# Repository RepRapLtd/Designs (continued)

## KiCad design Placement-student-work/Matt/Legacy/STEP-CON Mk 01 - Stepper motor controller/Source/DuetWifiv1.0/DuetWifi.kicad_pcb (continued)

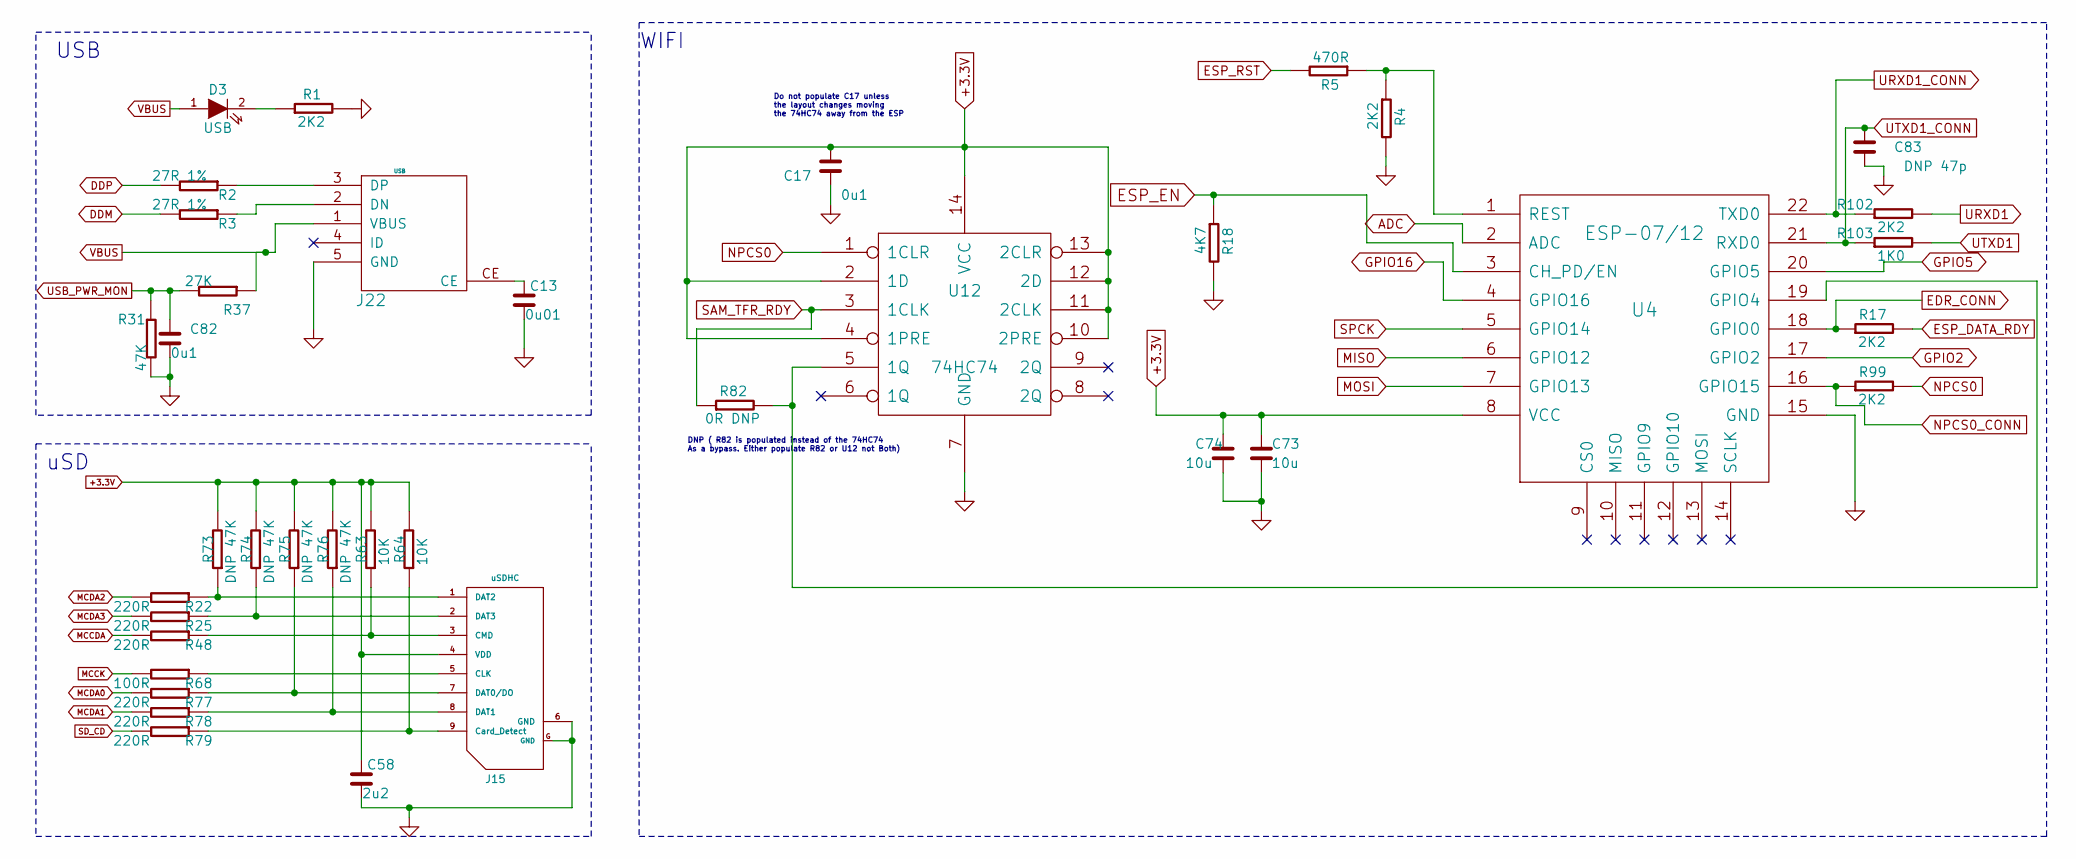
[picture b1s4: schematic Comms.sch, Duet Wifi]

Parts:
C13: 0u01; C_0603
C17, C82: 0u1; C_0603
C58: 2u2; C_0603
C73, C74: 10u; C_0805
C83: DNP 47p; C_0603
D3: USB; D_0603
J15: uSDHC; uSD_SKT
J22: USB; uUSB_new
R1, R4, R17, R99, R102: 2K2; R_0603
R2, R3: 27R 1%; R_0603
R5: 470R; R_0603
R18: 4K7; R_0603
R22, R25, R48, R77, R78, R79: 220R; R_0603
R31: 47K; R_0603
R37: 27K; R_0603
R63, R64: 10K; R_0603
R68: 100R; R_0603
R73, R74, R75, R76: DNP 47K; R_0603
R82: 0R DNP; R_0603
R103: 1K0; R_0603
U4: ESP-07/12; ESP-12E
U12: 74HC74; TSSOP-14

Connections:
+3.3V: C17.1, C58.1, C73.1, C74.1, J15.4 (VDD), R63.2, R64.2, R73.2, R74.2, R75.2, R76.2, U4.8 (VCC), U12.2 (1D), U12.4 (1PRE), U12.10 (2PRE), U12.11 (2CLK), U12.12 (2D), U12.13 (2CLR), U12.14 (VCC); also elsewhere on the board
ADC: U4.2 (ADC); also elsewhere on the board
DDM: R3.2; also elsewhere on the board
DDP: R2.2; also elsewhere on the board
EDR_CONN: R17.1, U4.18 (GPIO0); also elsewhere on the board
ESP_DATA_RDY: R17.2; also elsewhere on the board
ESP_EN: R18.1, U4.3 (CH_PD/EN); also elsewhere on the board
ESP_RST: R5.2; also elsewhere on the board
GND: C13.2, C17.2, C58.2, C73.2, C74.2, C82.2, C83.2, J15.6 (GND), J15.G (GND), J22.5 (GND), R1.2, R4.2, R18.2, R31.2, U4.15 (GND), U12.7 (GND); also elsewhere on the board
GPIO2: U4.17 (GPIO2); also elsewhere on the board
GPIO5: U4.20 (GPIO5); also elsewhere on the board
GPIO16: U4.4 (GPIO16); also elsewhere on the board
MCCDA: R48.2; also elsewhere on the board
MCCK: R68.2; also elsewhere on the board
MCDA0: R77.2; also elsewhere on the board
MCDA1: R78.2; also elsewhere on the board
MCDA2: R22.2; also elsewhere on the board
MCDA3: R25.2; also elsewhere on the board
MISO: U4.6 (GPIO12); also elsewhere on the board
MOSI: U4.7 (GPIO13); also elsewhere on the board
NPCS0: R99.2, U12.1 (1CLR); also elsewhere on the board
NPCS0_CONN: R99.1, U4.16 (GPIO15); also elsewhere on the board
unnamed: C13.1, J22.CE
unnamed: D3.2 (K), R1.1
unnamed: J15.1 (DAT2), R22.1, R73.1
unnamed: J15.2 (DAT3), R25.1, R74.1
unnamed: J15.3 (CMD), R48.1, R63.1
unnamed: J15.5 (CLK), R68.1
unnamed: J15.7 (DAT0/DO), R75.1, R77.1
unnamed: J15.8 (DAT1), R76.1, R78.1
unnamed: J15.9 (Card_Detect), R64.1, R79.1
unnamed: J22.2 (DN), R3.1
unnamed: J22.3 (DP), R2.1
unnamed: R4.1, R5.1, U4.1 (REST)
unnamed: R82.2, U4.19 (GPIO4), U12.5 (1Q)
SAM_TFR_RDY: R82.1, U12.3 (1CLK); also elsewhere on the board
SD_CD: R79.2; also elsewhere on the board
SPCK: U4.5 (GPIO14); also elsewhere on the board
URXD1: R102.2; also elsewhere on the board
URXD1_CONN: R102.1, U4.22 (TXD0); also elsewhere on the board
USB_PWR_MON: C82.1, R31.1, R37.2; also elsewhere on the board
UTXD1: R103.2; also elsewhere on the board
UTXD1_CONN: C83.1, R103.1, U4.21 (RXD0); also elsewhere on the board
VBUS: D3.1 (A), J22.1 (VBUS), R37.1; also elsewhere on the board

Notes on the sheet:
uSD
WIFI
USB
DNP ( R82 is populated instead of the 74HC74 As a bypass. Either populate R82 or U12 not Both)
Do not populate C17 unless the layout changes moving the 74HC74 away from the ESP

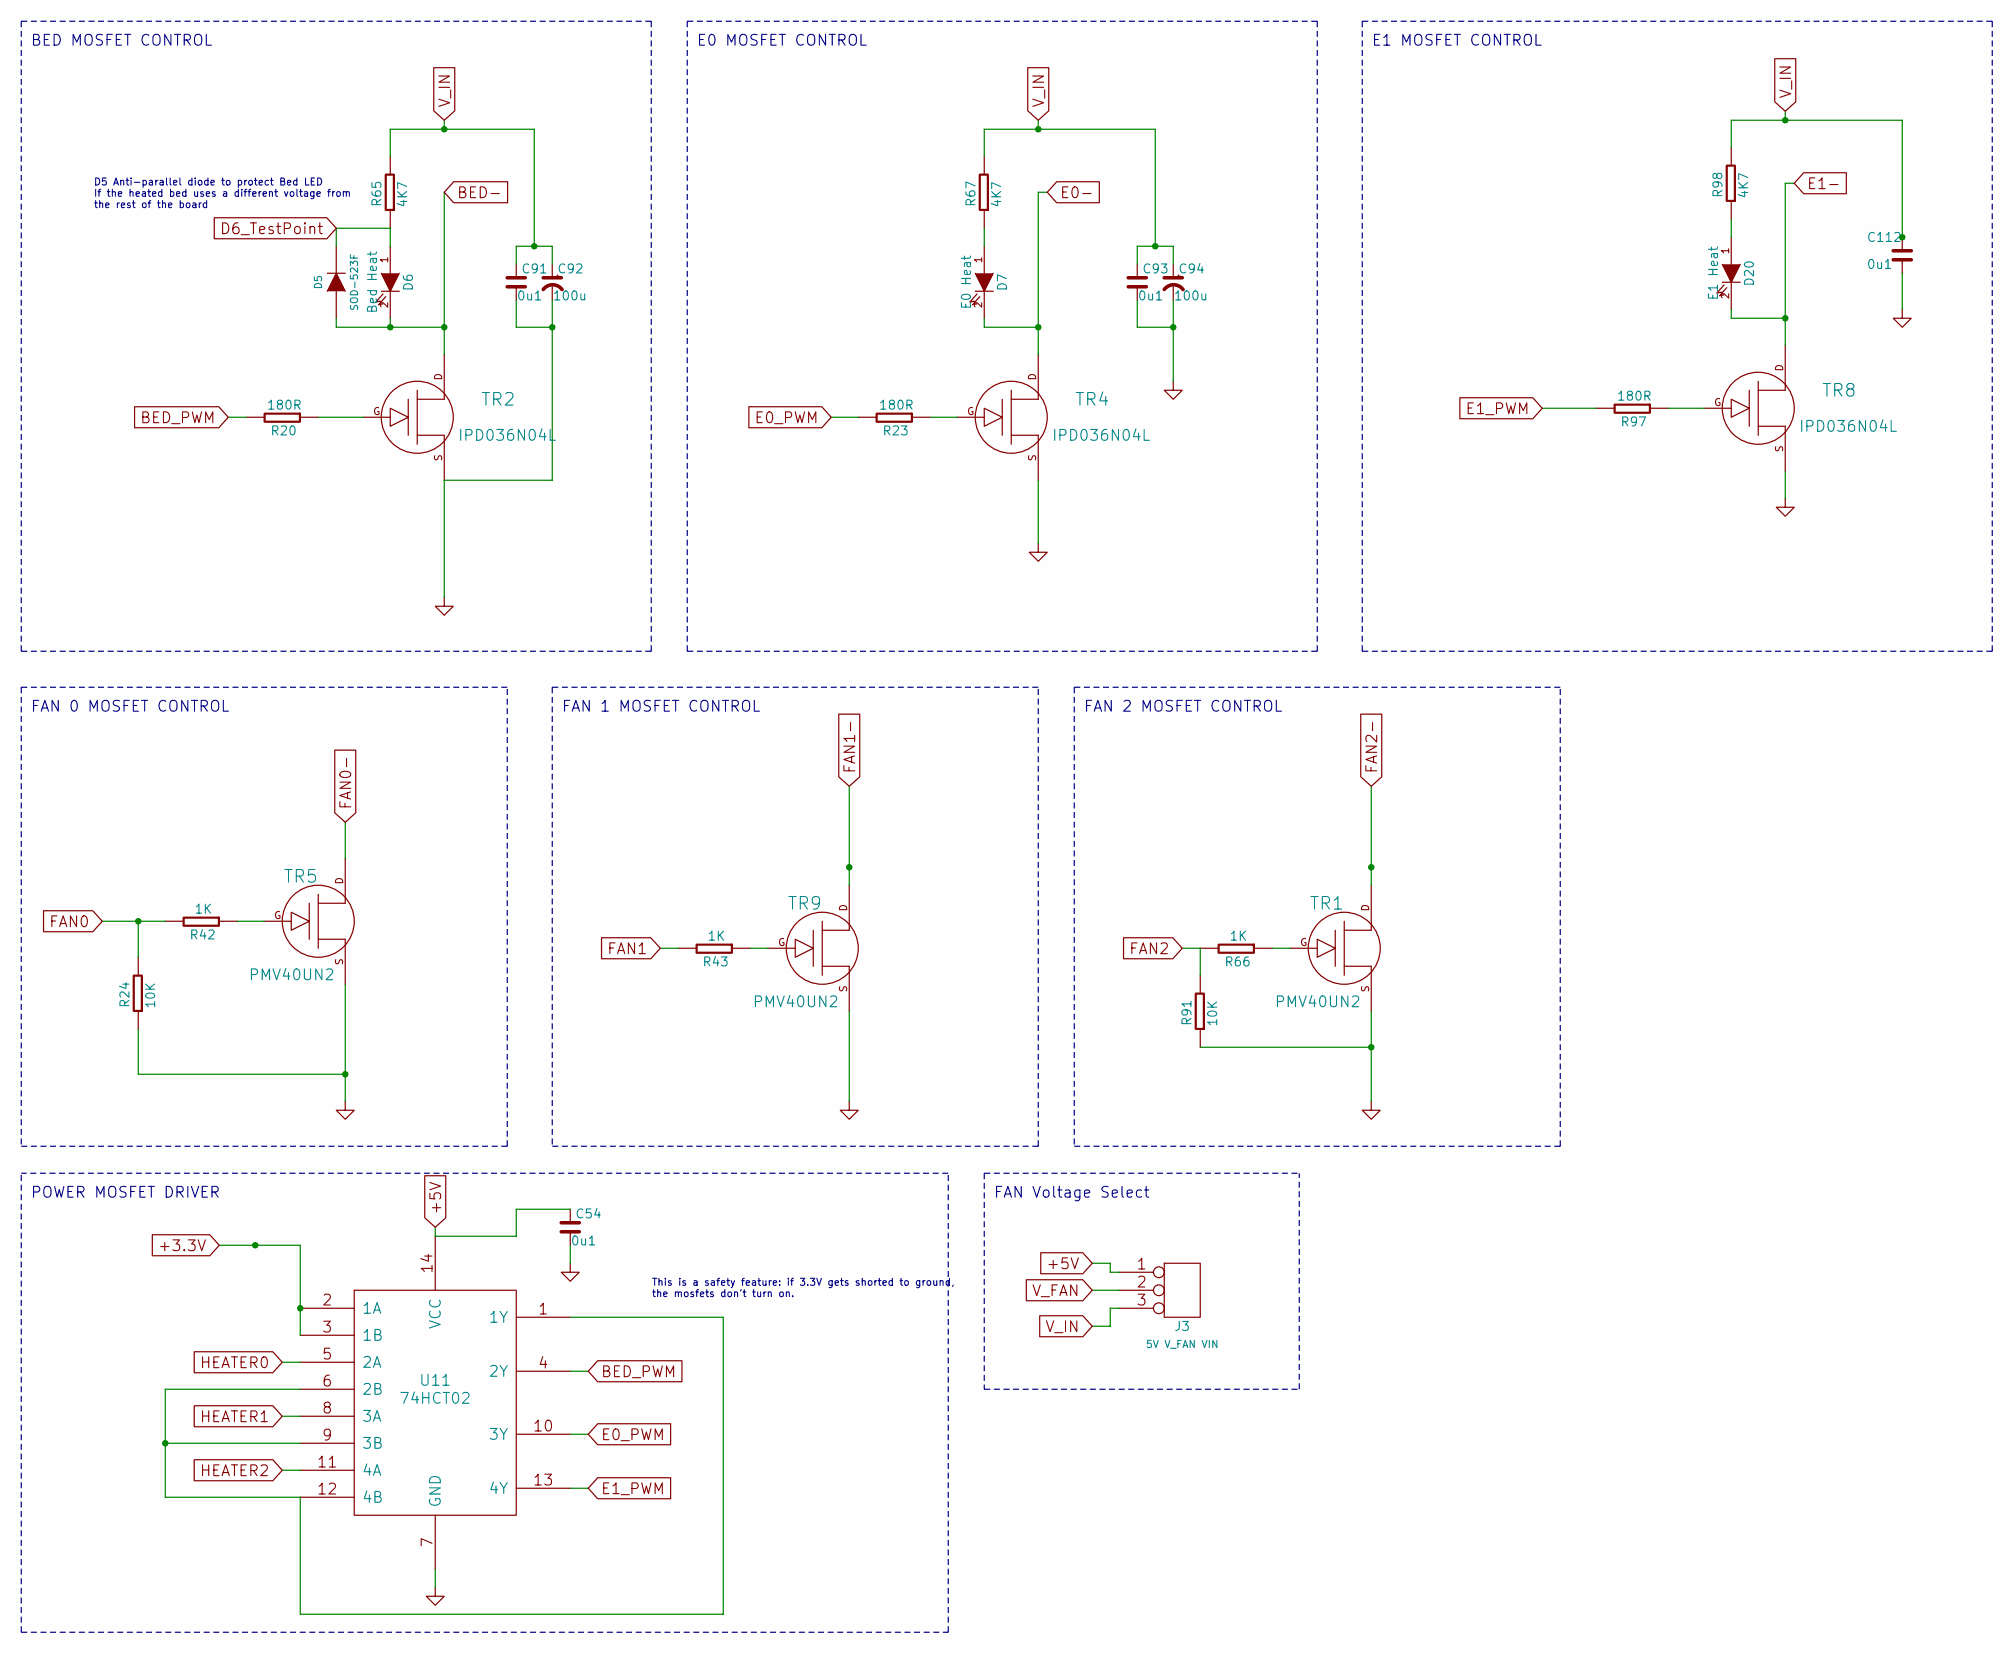
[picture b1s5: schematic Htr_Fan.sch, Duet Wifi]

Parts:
C54, C91, C93, C112: 0u1; C_0603
C92, C94: 100u; C_ELEC_6.3x7.7
D5: SOD-523F
D6: Bed Heat; D_0603
D7: E0 Heat; D_0603
D20: E1 Heat; D_0603
J3: 5V V_FAN VIN; CONN_3x1
R20, R23, R97: 180R; R_0603
R24, R91: 10K; R_0603
R42, R43, R66: 1K; R_0603
R65, R67, R98: 4K7; R_0603
TR1, TR5, TR9: PMV40UN2; SOT-23
TR2, TR4, TR8: IPD036N04L; D-PAK
U11: 74HCT02; TSSOP-14

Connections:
+3.3V: U11.2 (1A), U11.3 (1B); also elsewhere on the board
+5V: C54.1, J3.1, U11.14 (VCC); also elsewhere on the board
BED-: D5.2 (A), D6.2 (K), TR2.D; also elsewhere on the board
BED_PWM: R20.2, U11.4 (2Y); also elsewhere on the board
D6_TestPoint: D5.1 (K), D6.1 (A), R65.1; also elsewhere on the board
E0-: D7.2 (K), TR4.D; also elsewhere on the board
E0_PWM: R23.2, U11.10 (3Y); also elsewhere on the board
E1-: D20.2 (K), TR8.D; also elsewhere on the board
E1_PWM: R97.2, U11.13 (4Y); also elsewhere on the board
FAN0: R24.2, R42.2; also elsewhere on the board
FAN0-: TR5.D; also elsewhere on the board
FAN1: R43.2; also elsewhere on the board
FAN1-: TR9.D; also elsewhere on the board
FAN2: R66.2, R91.2; also elsewhere on the board
FAN2-: TR1.D; also elsewhere on the board
GND: C54.2, C91.2, C92.2, C93.2, C94.2, C112.2, R24.1, R91.1, TR1.S, TR2.S, TR4.S, TR5.S, TR8.S, TR9.S, U11.7 (GND); also elsewhere on the board
HEATER0: U11.5 (2A); also elsewhere on the board
HEATER1: U11.8 (3A); also elsewhere on the board
HEATER2: U11.11 (4A); also elsewhere on the board
unnamed: D7.1 (A), R67.1
unnamed: D20.1 (A), R98.1
unnamed: R20.1, TR2.G
unnamed: R23.1, TR4.G
unnamed: R42.1, TR5.G
unnamed: R43.1, TR9.G
unnamed: R66.1, TR1.G
unnamed: R97.1, TR8.G
unnamed: U11.1 (1Y), U11.6 (2B), U11.9 (3B), U11.12 (4B)
V_FAN: J3.2 (PM); also elsewhere on the board
V_IN: C91.1, C92.1, C93.1, C94.1, C112.1, J3.3, R65.2, R67.2, R98.2; also elsewhere on the board

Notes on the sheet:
FAN 0 MOSFET CONTROL
E0 MOSFET CONTROL
BED MOSFET CONTROL
E1 MOSFET CONTROL
FAN 1 MOSFET CONTROL
POWER MOSFET DRIVER
This is a safety feature: if 3.3V gets shorted to ground, the mosfets don't turn on.
FAN 2 MOSFET CONTROL
D5 Anti-parallel diode to protect Bed LED If the heated bed uses a different voltage from the rest of the board
FAN Voltage Select

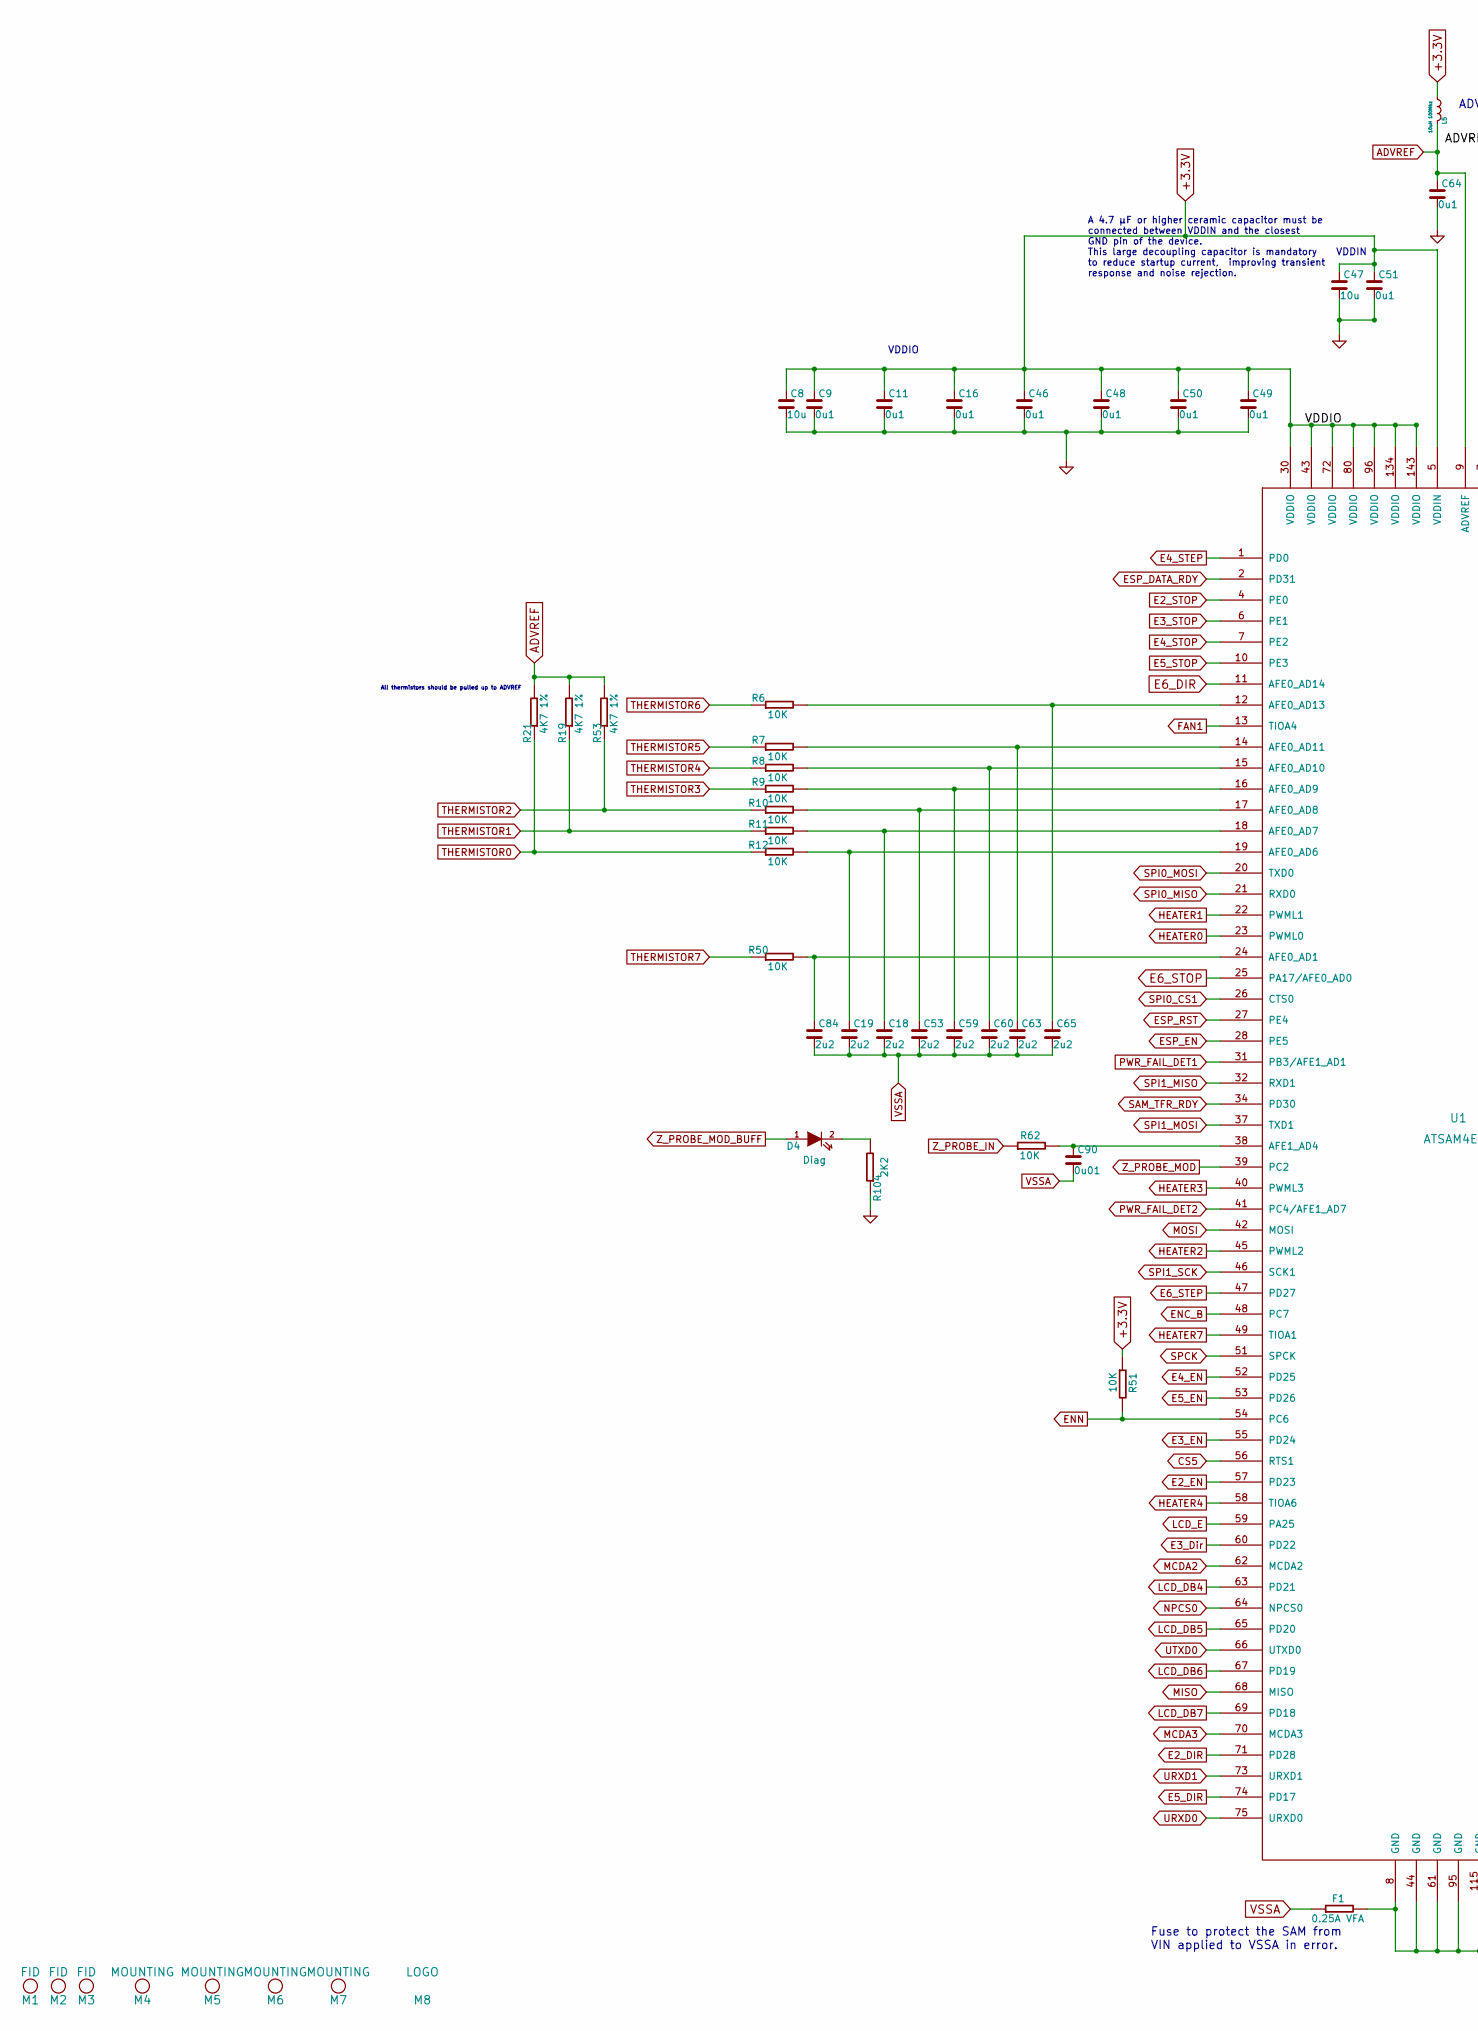
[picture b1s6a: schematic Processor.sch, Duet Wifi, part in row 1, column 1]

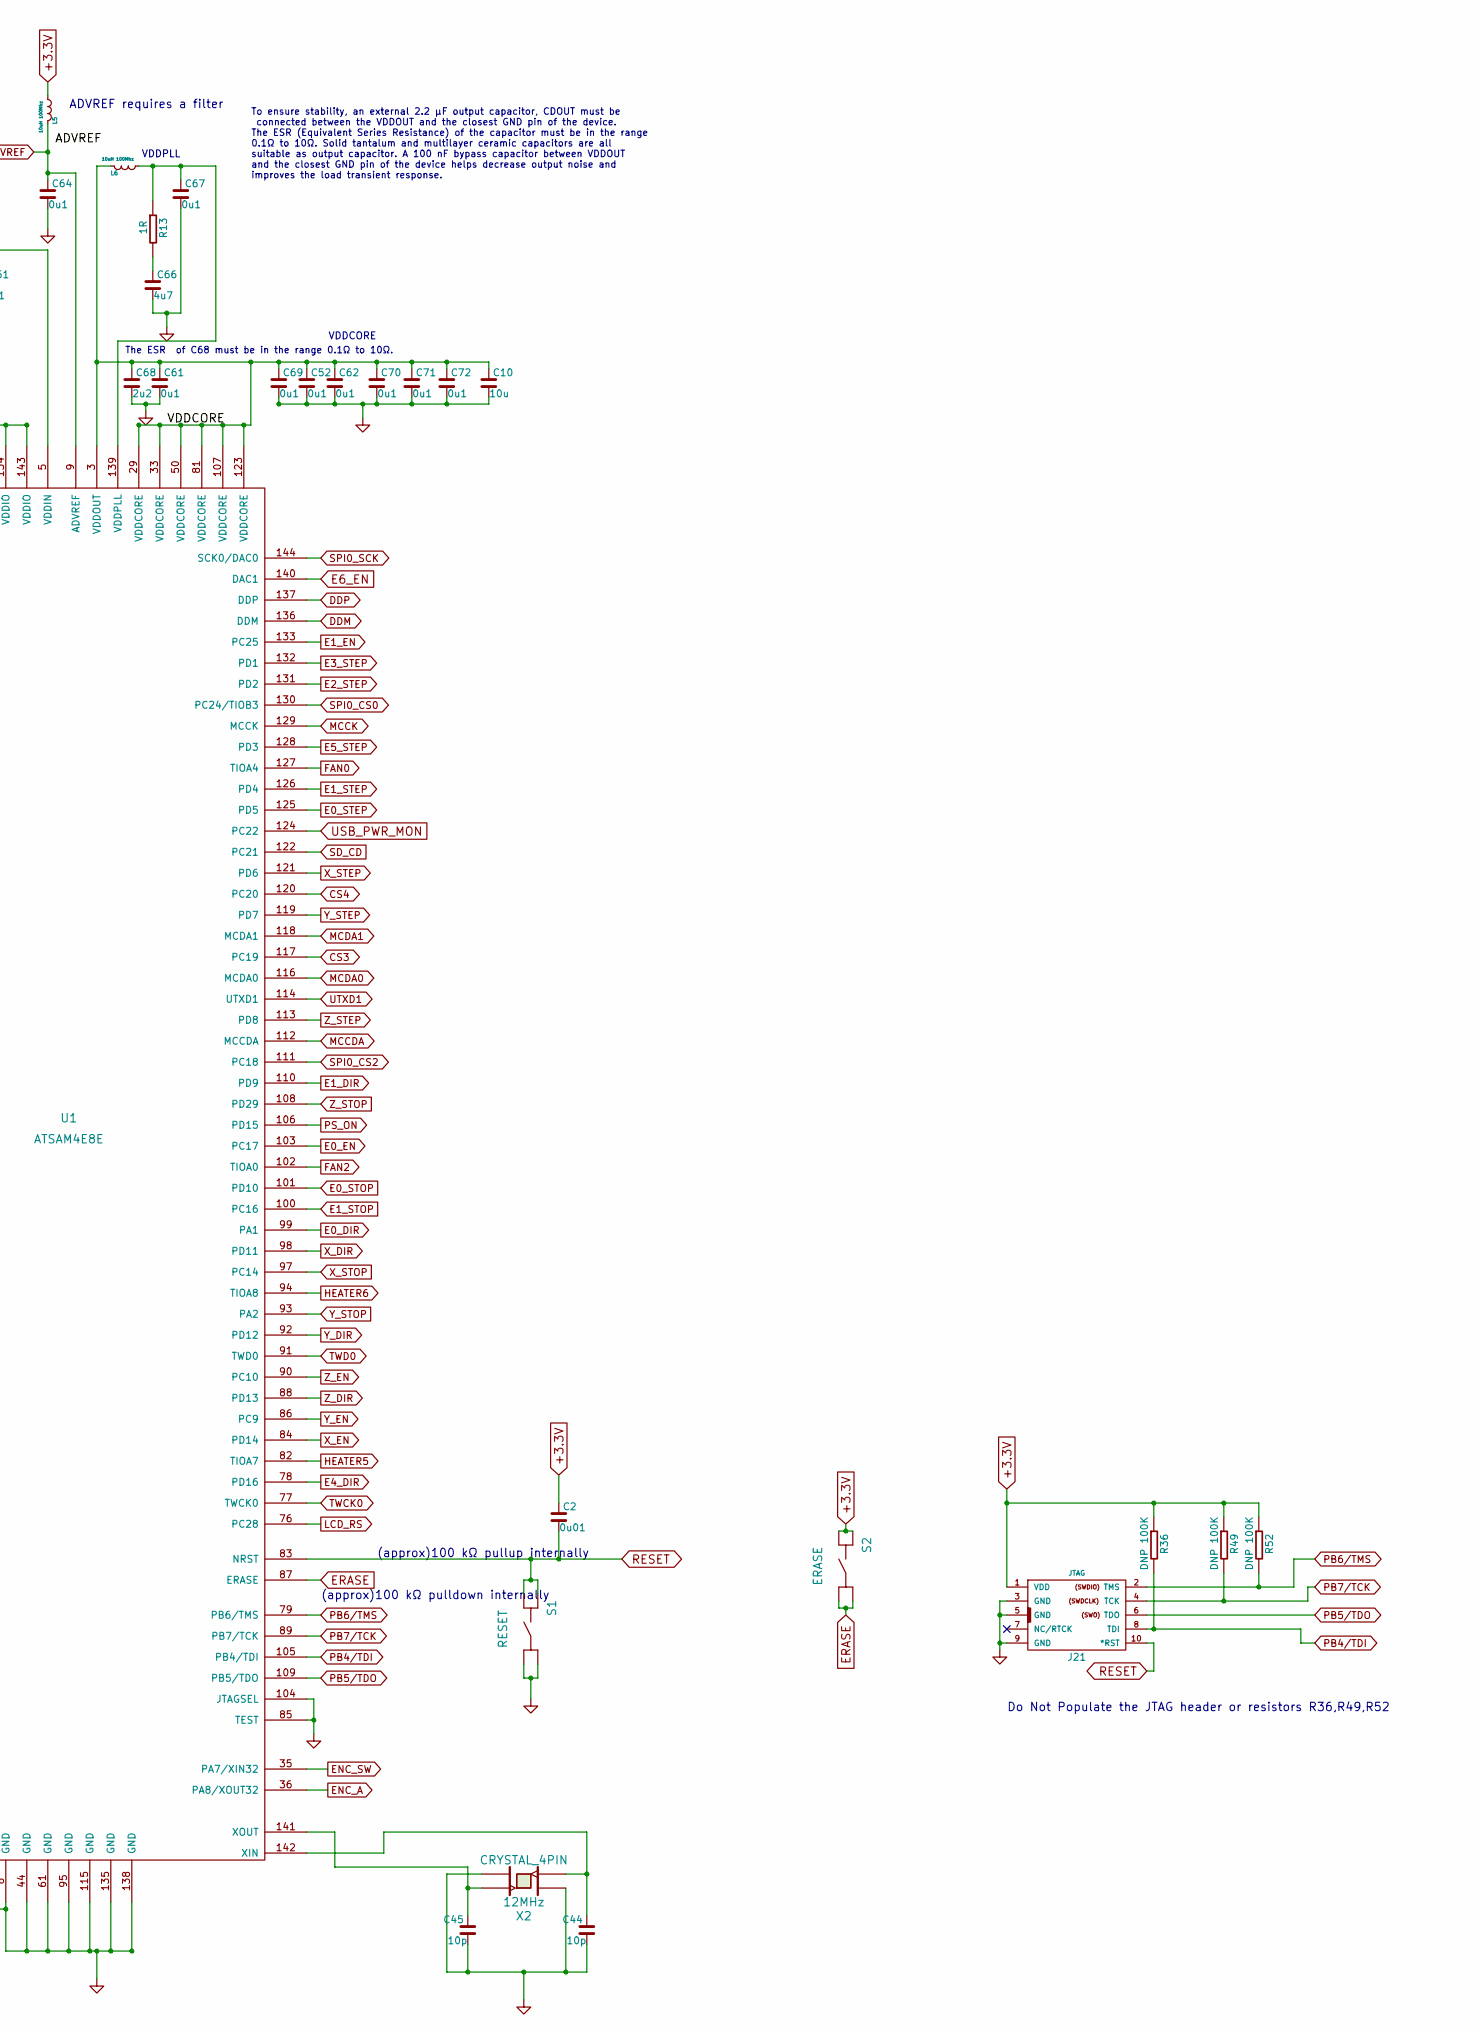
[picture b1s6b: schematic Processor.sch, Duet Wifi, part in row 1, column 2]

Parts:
C2, C90: 0u01; C_0603
C8, C10, C47: 10u; C_0805
C9, C11, C16, C46, C48, C49, C50, C51, C52, C61, C62, C64, C67, C69, C70, C71, C72: 0u1; C_0603
C18, C19, C53, C59, C60, C63, C65, C68, C84: 2u2; C_0603
C44, C45: 10p; C_0603
C66: 4u7; C_0805
D4: Diag; D_0603
F1: 0.25A VFA; FUSE_0603
J21: JTAG; MICRO_5x2
L5, L6: 10uH 100Mhz; R_0603
M1, M2, M3: FID; Fiducial_1mm_Dia_2.54mm_Outer_CopperTop
M4, M5, M6, M7: MOUNTING; Fixing_M4
M8: LOGO
R6, R7, R8, R9, R10, R11, R12, R50, R51, R62: 10K; R_0603
R13: 1R; R_0603
R19, R21, R53: 4K7 1%; R_0603
R36, R49, R52: DNP 100K; R_0603
R104: 2K2; R_0603
S1: RESET; SW_SIDE_1_lugs
S2: ERASE; SW_SIDE_1_lugs
U1: ATSAM4E8E; LQFP144
X2: CRYSTAL_4PIN; Xtal_5x3.2

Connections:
+3.3V: C2.1, C8.1, C9.1, C11.1, C16.1, C46.1, C47.1, C48.1, C49.1, C50.1, C51.1, J21.1 (VDD), L5.2 (B), R36.1, R49.1, R51.1, R52.1, S2.3, S2.4, U1.5 (VDDIN), U1.30 (VDDIO), U1.43 (VDDIO), U1.72 (VDDIO), U1.80 (VDDIO), U1.96 (VDDIO), U1.134 (VDDIO), U1.143 (VDDIO); also elsewhere on the board
/Processor/VDDCORE: C10.1, C52.1, C61.1, C62.1, C68.1, C69.1, C70.1, C71.1, C72.1, L6.1 (A), U1.3 (VDDOUT), U1.29 (VDDCORE), U1.33 (VDDCORE), U1.50 (VDDCORE), U1.81 (VDDCORE), U1.107 (VDDCORE), U1.123 (VDDCORE)
ADVREF: C64.1, L5.1 (A), R19.2, R21.2, R53.2, U1.9 (ADVREF); also elsewhere on the board
CS3: U1.117 (PC19); also elsewhere on the board
CS4: U1.120 (PC20); also elsewhere on the board
CS5: U1.56 (RTS1); also elsewhere on the board
DDM: U1.136 (DDM); also elsewhere on the board
DDP: U1.137 (DDP); also elsewhere on the board
E0_DIR: U1.99 (PA1); also elsewhere on the board
E0_EN: U1.103 (PC17); also elsewhere on the board
E0_STEP: U1.125 (PD5); also elsewhere on the board
E0_STOP: U1.101 (PD10); also elsewhere on the board
E1_DIR: U1.110 (PD9); also elsewhere on the board
E1_EN: U1.133 (PC25); also elsewhere on the board
E1_STEP: U1.126 (PD4); also elsewhere on the board
E1_STOP: U1.100 (PC16); also elsewhere on the board
E2_DIR: U1.71 (PD28); also elsewhere on the board
E2_EN: U1.57 (PD23); also elsewhere on the board
E2_STEP: U1.131 (PD2); also elsewhere on the board
E2_STOP: U1.4 (PE0); also elsewhere on the board
E3_DIR: U1.60 (PD22); also elsewhere on the board
E3_EN: U1.55 (PD24); also elsewhere on the board
E3_STEP: U1.132 (PD1); also elsewhere on the board
E3_STOP: U1.6 (PE1); also elsewhere on the board
E4_DIR: U1.78 (PD16); also elsewhere on the board
E4_EN: U1.52 (PD25); also elsewhere on the board
E4_STEP: U1.1 (PD0); also elsewhere on the board
E4_STOP: U1.7 (PE2); also elsewhere on the board
E5_DIR: U1.74 (PD17); also elsewhere on the board
E5_EN: U1.53 (PD26); also elsewhere on the board
E5_STEP: U1.128 (PD3); also elsewhere on the board
E5_STOP: U1.10 (PE3); also elsewhere on the board
E6_DIR: U1.11 (AFE0_AD14); also elsewhere on the board
E6_EN: U1.140 (DAC1); also elsewhere on the board
E6_STEP: U1.47 (PD27); also elsewhere on the board
E6_STOP: U1.25 (PA17/AFE0_AD0); also elsewhere on the board
ENC_A: U1.36 (PA8/XOUT32); also elsewhere on the board
ENC_B: U1.48 (PC7); also elsewhere on the board
ENC_SW: U1.35 (PA7/XIN32); also elsewhere on the board
ENN: R51.2, U1.54 (PC6); also elsewhere on the board
ERASE: S2.1, S2.2, U1.87 (ERASE)
ESP_DATA_RDY: U1.2 (PD31); also elsewhere on the board
ESP_EN: U1.28 (PE5); also elsewhere on the board
ESP_RST: U1.27 (PE4); also elsewhere on the board
FAN0: U1.127 (TIOA4); also elsewhere on the board
FAN1: U1.13 (TIOA4); also elsewhere on the board
FAN2: U1.102 (TIOA0); also elsewhere on the board
GND: C8.2, C9.2, C10.2, C11.2, C16.2, C44.2, C45.2, C46.2, C47.2, C48.2, C49.2, C50.2, C51.2, C52.2, C61.2, C62.2, C64.2, C66.2, C67.2, C68.2, C69.2, C70.2, C71.2, C72.2, F1.2, J21.3 (GND), J21.5 (GND), J21.9 (GND), R104.1, S1.1, S1.2, U1.8 (GND), U1.44 (GND), U1.61 (GND), U1.85 (TEST), U1.95 (GND), U1.104 (JTAGSEL), U1.115 (GND), U1.135 (GND), U1.138 (GND), X2.2, X2.4; also elsewhere on the board
HEATER0: U1.23 (PWML0); also elsewhere on the board
HEATER1: U1.22 (PWML1); also elsewhere on the board
HEATER2: U1.45 (PWML2); also elsewhere on the board
HEATER3: U1.40 (PWML3); also elsewhere on the board
HEATER4: U1.58 (TIOA6); also elsewhere on the board
HEATER5: U1.82 (TIOA7); also elsewhere on the board
HEATER6: U1.94 (TIOA8); also elsewhere on the board
HEATER7: U1.49 (TIOA1); also elsewhere on the board
LCD_DB4: U1.63 (PD21); also elsewhere on the board
LCD_DB5: U1.65 (PD20); also elsewhere on the board
LCD_DB6: U1.67 (PD19); also elsewhere on the board
LCD_DB7: U1.69 (PD18); also elsewhere on the board
LCD_E: U1.59 (PA25); also elsewhere on the board
LCD_RS: U1.76 (PC28); also elsewhere on the board
MCCDA: U1.112 (MCCDA); also elsewhere on the board
MCCK: U1.129 (MCCK); also elsewhere on the board
MCDA0: U1.116 (MCDA0); also elsewhere on the board
MCDA1: U1.118 (MCDA1); also elsewhere on the board
MCDA2: U1.62 (MCDA2); also elsewhere on the board
MCDA3: U1.70 (MCDA3); also elsewhere on the board
MISO: U1.68 (MISO); also elsewhere on the board
MOSI: U1.42 (MOSI); also elsewhere on the board
NPCS0: U1.64 (NPCS0); also elsewhere on the board
unnamed: C18.1, R11.2, U1.18 (AFE0_AD7)
unnamed: C19.1, R12.2, U1.19 (AFE0_AD6)
unnamed: C44.1, U1.142 (XIN), X2.3
unnamed: C45.1, U1.141 (XOUT), X2.1
unnamed: C53.1, R10.2, U1.17 (AFE0_AD8)
unnamed: C59.1, R9.2, U1.16 (AFE0_AD9)
unnamed: C60.1, R8.2, U1.15 (AFE0_AD10)
unnamed: C63.1, R7.2, U1.14 (AFE0_AD11)
unnamed: C65.1, R6.2, U1.12 (AFE0_AD13)
unnamed: C66.1, R13.2
unnamed: C67.1, L6.2 (B), R13.1, U1.139 (VDDPLL)
unnamed: C84.1, R50.2, U1.24 (AFE0_AD1)
unnamed: C90.1, R62.2, U1.38 (AFE1_AD4)
unnamed: D4.2 (K), R104.2
PB4/TDI: J21.8 (TDI), R36.2, U1.105 (PB4/TDI)
PB5/TDO: J21.6 (TDO), U1.109 (PB5/TDO)
PB6/TMS: J21.2 (TMS), R52.2, U1.79 (PB6/TMS); also elsewhere on the board
PB7/TCK: J21.4 (TCK), R49.2, U1.89 (PB7/TCK)
PS_ON: U1.106 (PD15); also elsewhere on the board
PWR_FAIL_DET1: U1.31 (PB3/AFE1_AD1); also elsewhere on the board
PWR_FAIL_DET2: U1.41 (PC4/AFE1_AD7); also elsewhere on the board
RESET: C2.2, J21.10 (*RST), S1.3, S1.4, U1.83 (NRST); also elsewhere on the board
SAM_TFR_RDY: U1.34 (PD30); also elsewhere on the board
SD_CD: U1.122 (PC21); also elsewhere on the board
SPCK: U1.51 (SPCK); also elsewhere on the board
SPI0_CS0: U1.130 (PC24/TIOB3); also elsewhere on the board
SPI0_CS1: U1.26 (CTS0); also elsewhere on the board
SPI0_CS2: U1.111 (PC18); also elsewhere on the board
SPI0_MISO: U1.21 (RXD0); also elsewhere on the board
SPI0_MOSI: U1.20 (TXD0); also elsewhere on the board
SPI0_SCK: U1.144 (SCK0/DAC0); also elsewhere on the board
SPI1_MISO: U1.32 (RXD1); also elsewhere on the board
SPI1_MOSI: U1.37 (TXD1); also elsewhere on the board
SPI1_SCK: U1.46 (SCK1); also elsewhere on the board
THERMISTOR0: R12.1, R21.1; also elsewhere on the board
THERMISTOR1: R11.1, R19.1; also elsewhere on the board
THERMISTOR2: R10.1, R53.1; also elsewhere on the board
THERMISTOR3: R9.1; also elsewhere on the board
THERMISTOR4: R8.1; also elsewhere on the board
THERMISTOR5: R7.1; also elsewhere on the board
THERMISTOR6: R6.1; also elsewhere on the board
THERMISTOR7: R50.1; also elsewhere on the board
TWCK0: U1.77 (TWCK0); also elsewhere on the board
TWD0: U1.91 (TWD0); also elsewhere on the board
URXD0: U1.75 (URXD0); also elsewhere on the board
URXD1: U1.73 (URXD1); also elsewhere on the board
USB_PWR_MON: U1.124 (PC22); also elsewhere on the board
UTXD0: U1.66 (UTXD0); also elsewhere on the board
UTXD1: U1.114 (UTXD1); also elsewhere on the board
VSSA: C18.2, C19.2, C53.2, C59.2, C60.2, C63.2, C65.2, C84.2, C90.2, F1.1; also elsewhere on the board
X_DIR: U1.98 (PD11); also elsewhere on the board
X_EN: U1.84 (PD14); also elsewhere on the board
X_STEP: U1.121 (PD6); also elsewhere on the board
X_STOP: U1.97 (PC14); also elsewhere on the board
Y_DIR: U1.92 (PD12); also elsewhere on the board
Y_EN: U1.86 (PC9); also elsewhere on the board
Y_STEP: U1.119 (PD7); also elsewhere on the board
Y_STOP: U1.93 (PA2); also elsewhere on the board
Z_DIR: U1.88 (PD13); also elsewhere on the board
Z_EN: U1.90 (PC10); also elsewhere on the board
Z_PROBE_IN: R62.1; also elsewhere on the board
Z_PROBE_MOD: U1.39 (PC2); also elsewhere on the board
Z_PROBE_MOD_BUFF: D4.1 (A); also elsewhere on the board
Z_STEP: U1.113 (PD8); also elsewhere on the board
Z_STOP: U1.108 (PD29); also elsewhere on the board

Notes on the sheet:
(approx)100 kΩ pullup internally
VDDPLL
VDDCORE
VDDIO
VDDIN
(approx)100 kΩ pulldown internally
A 4.7 μF or higher ceramic capacitor must be connected between VDDIN and the closest GND pin of the device. This large decoupling capacitor is mandatory to reduce startup current, improving transient response and noise rejection.
To ensure stability, an external 2.2 μF output capacitor, CDOUT must be connected between the VDDOUT and the closest GND pin of the device. The ESR (Equivalent Series Resistance) of the capacitor must be in the range 0.1Ω to 10Ω. Solid tantalum and multilayer ceramic capacitors are all suitable as 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
Fuse to protect the SAM from VIN applied to VSSA in error.
The ESR of C68 must be in the range 0.1Ω to 10Ω.
All thermistors should be pulled up to ADVREF
Do Not Populate the JTAG header or resistors R36,R49,R52
ADVREF requires a filter

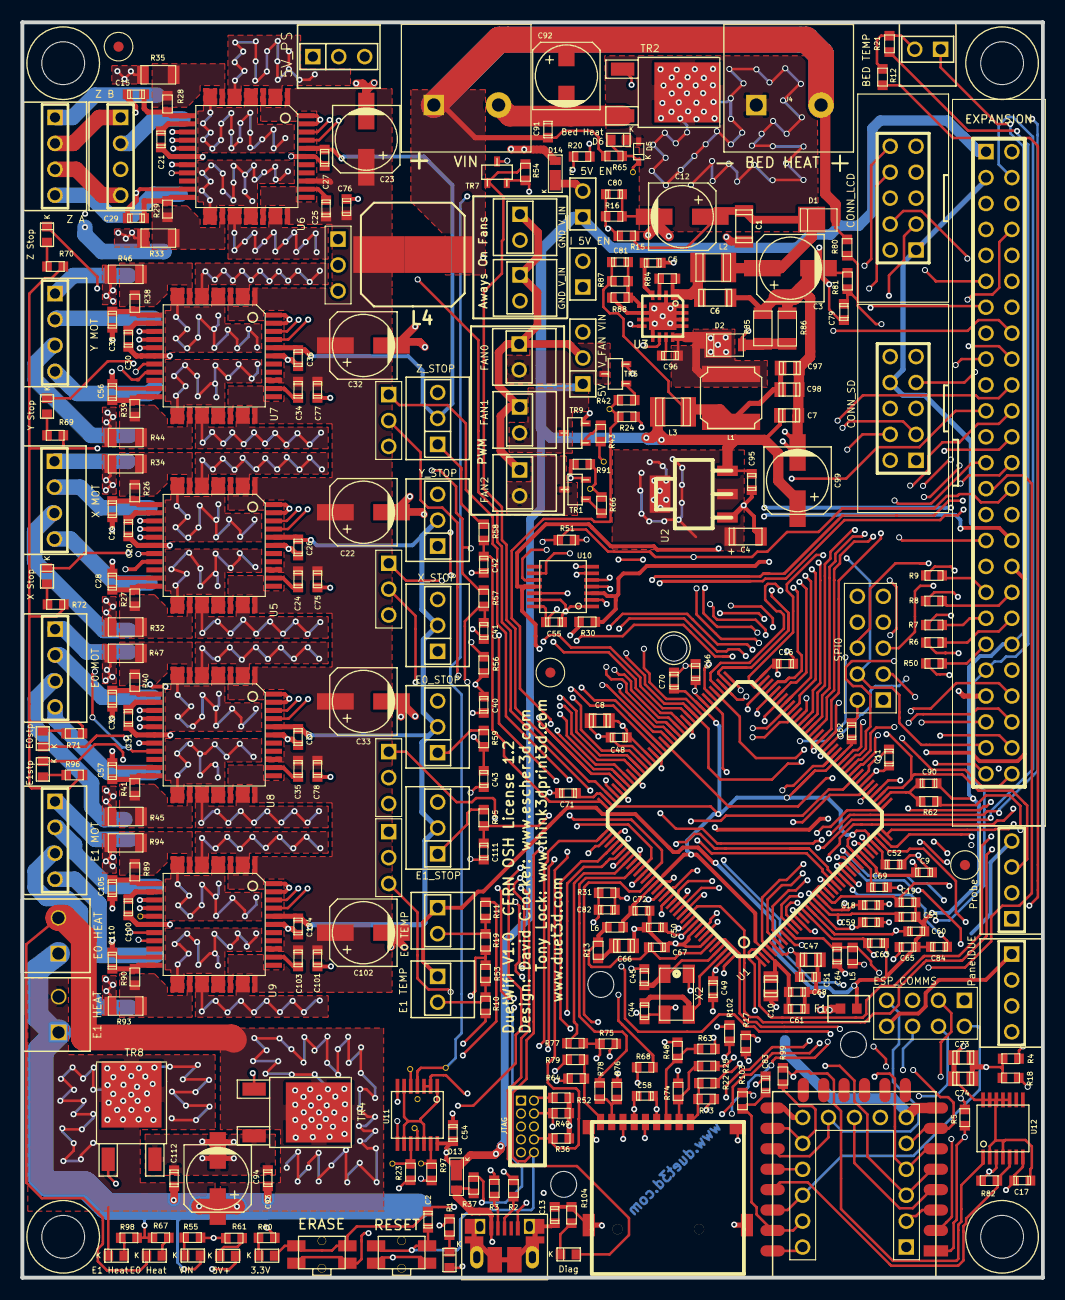
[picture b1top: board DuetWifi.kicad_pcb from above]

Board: 4 copper layers, 100.0 x 123.0 mm, 311 parts (1 on the bottom side), 262 nets.

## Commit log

2019-09-13 Sorting out move from old defunct account.
2024-05-29 Updating designs
2024-05-29 Updating...
2024-08-09 Added the Python air-vent macro.
2024-08-09 RM for vent
2024-08-09 spelling
2024-08-09 Now with PDF...
2024-10-07 Added air vent image etc.
